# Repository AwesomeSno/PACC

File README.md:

# Palma Advanced Cursor Control (PACC)

PACC is a glove based controller inspired by sci-fi movies that lets you control any device using your palm without ever touching a mouse. The idea is to have something similar to how you control things on an Apple Vision Pro, but for any regular computer or device.

## How it works

The glove uses an onboard IMU and flex sensors to track your hand orientation and finger movements, which an ESP32 translates into standard HID mouse commands sent over Bluetooth or USB-C.

### Hardware layout

- **IMU on the back of the hand / palm**: Tracks hand tilt and orientation in real time.
- **Flex sensors on fingers**: Detects bends, pinches, and finger taps.
- **ESP32 microcontroller**: Handles sensor data processing and sends mouse commands over Bluetooth HID or USB.
- **LiPo battery**: Powers the wearable from the wrist.

## Hardware & PCB Design

### Schematic
The complete custom circuit schematic features the ESP32-S3 microcontroller, BNO085 9-DOF IMU, TP4056 LiPo charging management, TLV75533P 3.3V LDO regulator, USB-C interface with CC pull-downs, tactile buttons for Boot and Reset, status LEDs, and an ERM haptic feedback motor driver with flyback diode protection.

*(Vector PDF available in [images/schematic.pdf](images/schematic.pdf))*

### PCB Design & 3D Renders
The custom PCB is designed as a compact 2-layer wearable board (60 mm × 40 mm) with a continuous ground plane, optimized high-frequency routing, and filtered power distribution. All 26 nets are fully routed with 0 DRC errors and 0 unconnected items.

| Top View (3D Render) | Isometric View (3D Render) |
| :---: | :---: |
|  |  |

| Bottom View (3D Render) | 2D Routing & Traces |
| :---: | :---: |
|  |  |

- **Fabrication Files**: Production-ready Gerbers and drill files are archived in [`gerbers.zip`](gerbers.zip) and [`fabrication/gerbers.zip`](fabrication/gerbers.zip).
- **Bill of Materials (BOM)**: Complete component list with part numbers, quantities, costs, and purchasing links is documented in [`BOM.md`](BOM.md) and [`BOM.csv`](BOM.csv).

## Firmware & Motion Control

The firmware located in [`firmware/pacc_firmware.ino`](firmware/pacc_firmware.ino) implements:
- Real-time sensor fusion using the onboard BNO085 (Game Rotation Vector / Angular Velocity at 50Hz).
- Adaptive deadzone filtering and non-linear cursor acceleration for sub-millimeter precision.
- Native Bluetooth Low Energy (BLE) HID mouse emulation via `BleMouse`.
- Haptic motor feedback confirmation on clicks.

## Planned gestures

The goal is to keep interactions natural and simple:

- **Tilt = Move**: Tilt your hand to move the cursor across the screen.
- **Pinch = Click**: Pinch your fingers together for a standard left click.
- **Tap = Right click**: Quick finger tap triggers a secondary right click.
- **Swipe = Scroll**: Swipe your hand to scroll through pages and documents.

## Multi-device control

One glove can stay paired with multiple devices at once (laptop, phone, tablet) so you can switch between screens seamlessly without having to disconnect and reconnect every time.

## Engineering challenges

Key things to solve during the build:

- **Battery life**: Keeping power consumption low while reading sensors and running Bluetooth.
- **Bluetooth delay**: Minimizing input latency so cursor movement feels snappy.
- **Sensor calibration**: Filtering noise and drift from the IMU.
- **Comfort**: Making the glove lightweight and easy to wear for long sessions.

## Future roadmap

This first prototype is built as a glove to test the sensors and tracking algorithms. Once everything works reliably, the long-term goal is to shrink the entire system down into a compact ring.

## Author

Designed and built by Harinandan J V for Hack Club's Half Life.

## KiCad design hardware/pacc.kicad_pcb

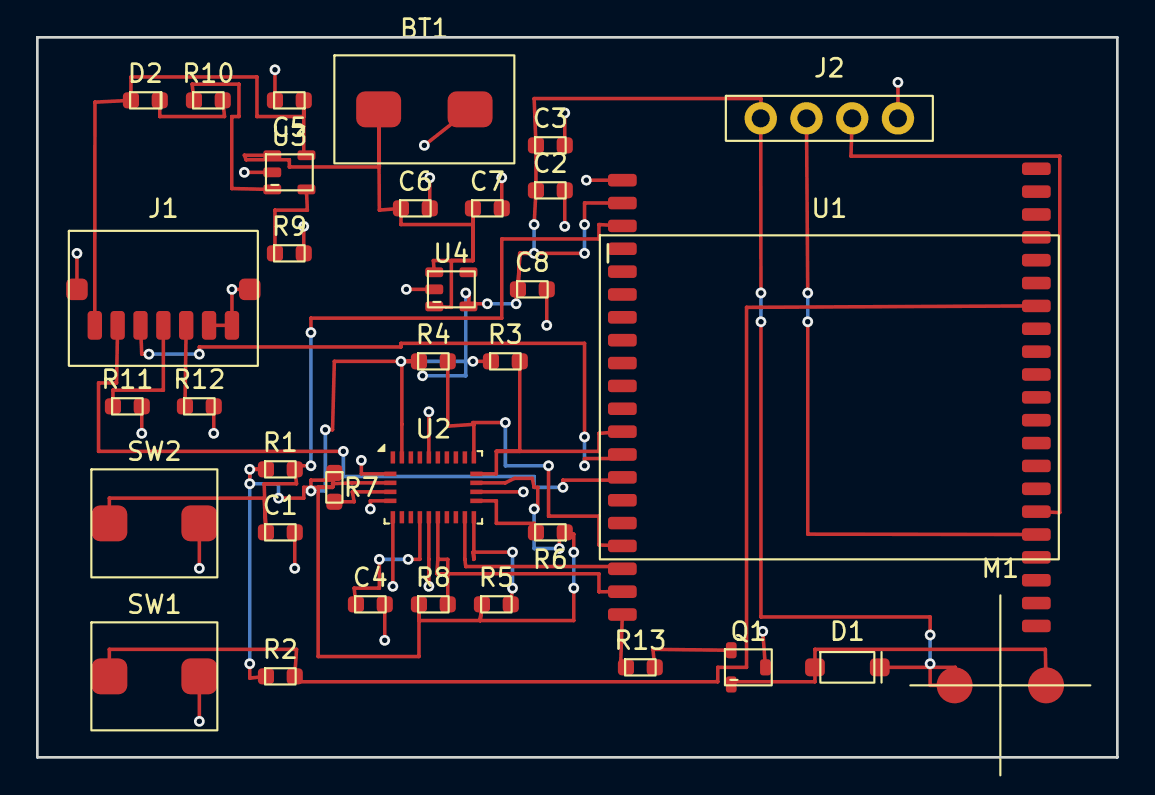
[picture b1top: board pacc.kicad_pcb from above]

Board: 2 copper layers, 60.0 x 40.0 mm, 34 parts (0 on the bottom side), 26 nets.

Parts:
BT1: 3.7V 500mAh; BatteryHolder
C1, C7, C8: 1u; C_0603_1608Metric
C2: 10u; C_0603_1608Metric
C3, C4: 100n; C_0603_1608Metric
C5, C6: 4.7u; C_0603_1608Metric
D1: 1N4148; D_SOD-123
D2: RED; LED_0603_1608Metric
J1: USB-C; USB_C_Receptacle
J2: DEBUG; Connector_PinHeader_1x04
M1: COIN; Motor_Coin
Q1: 2N2222; SOT-23
R1, R2, R5, R6, R7, R8: 10k; R_0603_1608Metric
R3, R4: 4.7k; R_0603_1608Metric
R9: 3.9k; R_0603_1608Metric
R10, R13: 1k; R_0603_1608Metric
R11, R12: 5.1k; R_0603_1608Metric
SW1: BOOT; SW_Tactile
SW2: RESET; SW_Tactile
U1: ESP32-S3-WROOM-1
U2: BNO085; LGA-28_5.2x3.8mm_P0.5mm
U3: MCP73831; SOT-23-5
U4: TLV75533P; SOT-23-5

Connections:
+3V3: C2.1, C3.1, C8.1, D1.2, J2.1, M1.1, R1.1, R2.1, R3.1, R4.1, R5.1, R6.1, R7.1, R8.1, U1.2, U2.3, U2.18, U2.28, U4.5
BOOT: R2.2, SW1.1, U1.27
BOOTN: R7.2, U2.4
CAP: C4.1, U2.9
CC1: J1.4, R11.1
CC2: J1.5, R12.1
DBG_RX: J2.3, U1.36
DBG_TX: J2.2, U1.37
EN: C1.1, R1.2, SW2.1, U1.3
ENV_SCL: R5.2, U2.15
ENV_SDA: R6.2, U2.16
GND: BT1.2, C1.2, C2.2, C3.2, C4.2, C5.2, C6.2, C7.2, C8.2, J1.6, J1.7, J1.S1, J1.S2, J2.4, Q1.3, R9.2, R11.2, R12.2, SW1.2, SW2.2, U1.1, U2.2, U2.5, U2.6, U2.10, U2.17, U2.25, U3.2, U4.2
IMU_INT: U1.18, U2.14
IMU_RST: R8.2, U1.19, U2.11
LEDK: D2.2, R10.2
MOTOR: R13.1, U1.20
MOTOR_B: Q1.2, R13.2
MOTOR_N: D1.1, M1.2, Q1.1
PROG: R9.1, U3.5
SCL: R3.2, U1.12, U2.19
SDA: R4.2, U1.17, U2.20
STAT: R10.1, U3.1
USB_DM: J1.3, U1.13
USB_DP: J1.2, U1.14
VBAT: BT1.1, C6.1, C7.1, U3.3, U4.1, U4.3
VBUS: C5.1, D2.1, J1.1, U3.4

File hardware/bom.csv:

Reference,Value,Footprint,Qty,UnitPrice,TotalPrice,Vendor,Link
"C3,C4","100nF 50V","Capacitor_SMD:C_0603_1608Metric",2,"$0.01","$0.02","LCSC","https://www.lcsc.com/product-detail/Multilayer-Ceramic-Capac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"
"R1,R2,R5,R6,R7,R8","10k 1%","Resistor_SMD:R_0603_1608Metric",6,"$0.005","$0.03","LCSC","https://www.lcsc.com/product-detail/Chip-Resistor-Surface-Mo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"
"C2","10uF 25V","Capacitor_SMD:C_0603_1608Metric",1,"$0.03","$0.03","LCSC","https://www.lcsc.com/product-detail/Multilayer-Ceramic-Capac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"
"D1","1N4148W","Diode_SMD:D_SOD-123",1,"$0.02","$0.02","LCSC","https://www.lcsc.com/product-detail/Diodes-General-Purpose_J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"
"R10,R13","1k 1%","Resistor_SMD:R_0603_1608Metric",2,"$0.005","$0.01","LCSC","https://www.lcsc.com/product-detail/Chip-Resistor-Surface-Mo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"
"C1,C7,C8","1uF 50V","Capacitor_SMD:C_0603_1608Metric",3,"$0.01","$0.03","LCSC","https://www.lcsc.com/product-detail/Multilayer-Ceramic-Capac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"
"Q1","MMBT2222A","Package_TO_SOT_SMD:SOT-23",1,"$0.03","$0.03","LCSC","https://www.lcsc.com/product-detail/Bipolar-Transistors-BJT_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"
"BT1","3.7V 500mAh LiPo","BatteryHolder",1,"$3.50","$3.50","Robu.in","https://robu.in/product/3-7v-500mah-lipo-rechargeable-battery/"
"R9","3.9k 1%","Resistor_SMD:R_0603_1608Metric",1,"$0.005","$0.01","LCSC","https://www.lcsc.com/product-detail/Chip-Resistor-Surface-Mo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"
"R3,R4","4.7k 1%","Resistor_SMD:R_0603_1608Metric",2,"$0.005","$0.01","LCSC","https://www.lcsc.com/product-detail/Chip-Resistor-Surface-Mo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"
"C5,C6","4.7uF 25V","Capacitor_SMD:C_0603_1608Metric",2,"$0.02","$0.04","LCSC","https://www.lcsc.com/product-detail/Multilayer-Ceramic-Capac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"
"R11,R12","5.1k 1%","Resistor_SMD:R_0603_1608Metric",2,"$0.005","$0.01","LCSC","https://www.lcsc.com/product-detail/Chip-Resistor-Surface-Mo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"
"U2","BNO085","Palma:BNO085_LGA28",1,"$21.89","$21.89","Robocraze","https://robocraze.com/products/bno085-9-dof-orientation-imu-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"
"SW1","BOOT (TS-1187A)","SW_Tactile",1,"$0.05","$0.05","LCSC","https://www.lcsc.com/product-detail/Tactile-Switches_XKB-Ent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"
"M1","1027 3V Coin Motor","Motor_Coin",1,"$0.51","$0.51","Robu.in","https://robu.in/product/1027%203V%20Flat%20Mobile%20Phone%20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"
"J2","DEBUG 1x04 2.54mm","Connector_PinHeader_1x04",1,"$0.05","$0.05","LCSC","https://www.lcsc.com/product-detail/Pin-Headers_BOOMELE-Boom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"
"U1","ESP32-S3-WROOM-1","RF_Module:ESP32-S3-WROOM-1",1,"$3.40","$3.40","LCSC","https://www.lcsc.com/product-detail/WiFi-Modules_Espressif-S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"
"U3","MCP73831T-2ACI/OT","Package_TO_SOT_SMD:SOT-23-5",1,"$0.78","$0.78","LCSC","https://www.lcsc.com/product-detail/Battery-Management-ICs_M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"
"D2","RED 0603 LED","LED_SMD:LED_0603_1608Metric",1,"$0.02","$0.02","LCSC","https://www.lcsc.com/product-detail/Light-Emitting-Diodes-LE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"
"SW2","RESET (TS-1187A)","SW_Tactile",1,"$0.05","$0.05","LCSC","https://www.lcsc.com/product-detail/Tactile-Switches_XKB-Ent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"
"U4","TLV75533PDBVR","Package_TO_SOT_SMD:SOT-23-5",1,"$0.14","$0.14","LCSC","https://www.lcsc.com/product-detail/Linear-Voltage-Regulator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"
"J1","USB-C TYPE-C-31-M-12","Connector_USB:USB_C_Receptacle",1,"$0.17","$0.17","LCSC","https://www.lcsc.com/product-detail/USB-Connectors_Korean-Hr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"
